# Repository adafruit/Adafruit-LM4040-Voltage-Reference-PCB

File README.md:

## Adafruit LM4040 Voltage Reference PCB
<a href="http://www.adafruit.com/products/2200"><br/>
Click here to purchase one from the Adafruit shop</a>

How good is your multimeter really?  Or maybe your analog converter needs a good reference? Or lets say you want to test your microcontroller's conversion accuracy & precision. If only you had a dependable, high precision, rock-solid voltage reference. Now you know why we made this very cute and useful little breakout board. It has two very high precision shunt-type voltage references with 750 ohm biasing resistors. One is 2.048V (great for 3.3V reference systems) and the other is 4.096 (great for 5V). Both are 0.1% accuracy!

Using is easy, just power with about 5V-12V, or 3V if you want only the 2V reference to work. Then measure the voltage on the output. Note that these are not regulators - you can't power anything off the output. They are for measurements only. For more details, check the LM4040 Datasheet for more information.

PCB files for the Adafruit LM4040 Voltage Reference. The format is EagleCAD schematic and board layout
- https://www.adafruit.com/products/2200

### License

Adafruit invests time and resources providing this open source design, please support Adafruit and open-source hardware by purchasing products from [Adafruit](https://www.adafruit.com)!

All text above must be included in any redistribution

Designed by Limor Fried/Ladyada for Adafruit Industries.
Creative Commons Attribution/Share-Alike, all text above must be included in any redistribution. 
See license.txt for additional information.

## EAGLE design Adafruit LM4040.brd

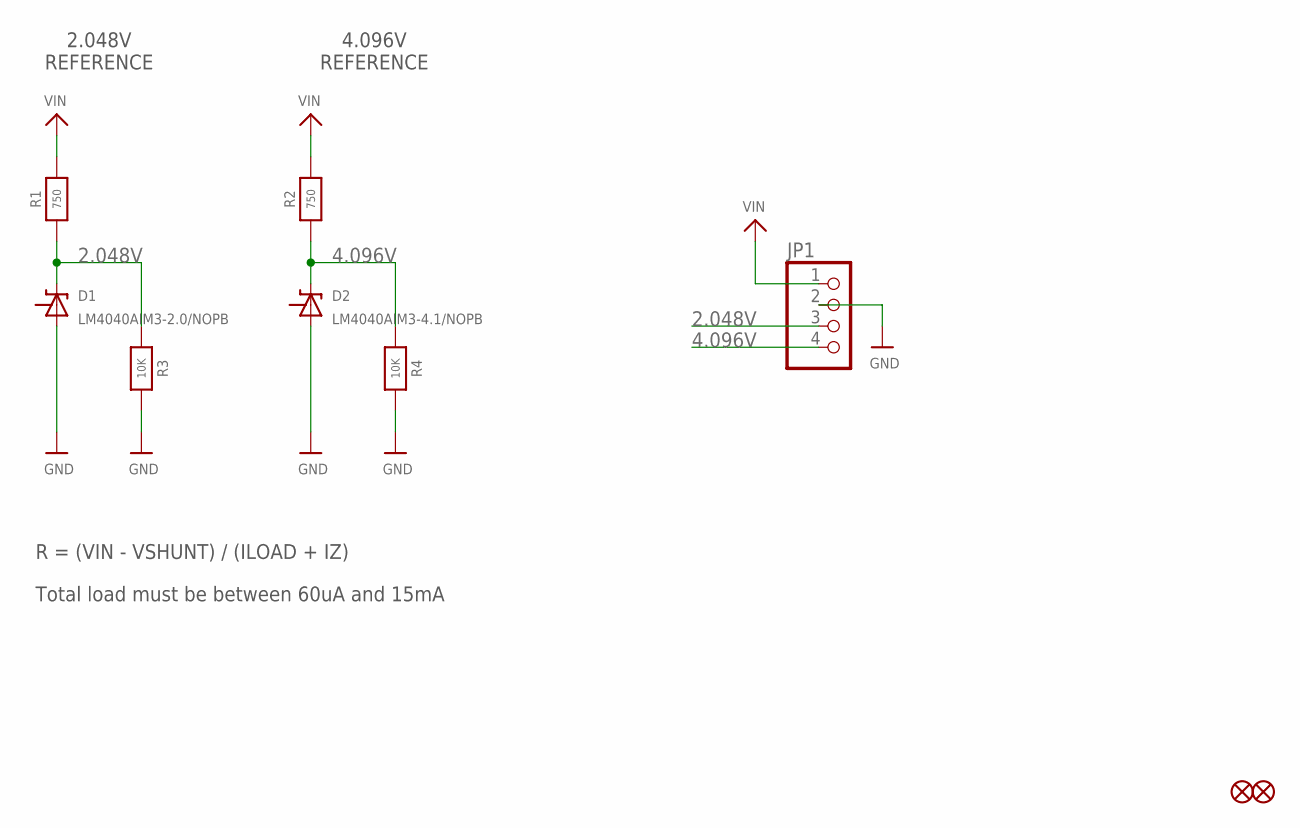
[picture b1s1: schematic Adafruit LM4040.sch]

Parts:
D1: LM4040AIM3-2.0/NOPB; SOT23-R
D2: LM4040AIM3-4.1/NOPB; SOT23-R
FID1, FID2: FIDUCIAL""; FIDUCIAL_1MM
JP1: HEADER-1X4ROUND; 1X04_ROUND
R1, R2: 750; 0805-NO
R3, R4: 10K; 0805-NO

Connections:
2.048V: D1.1 (+), JP1.3, R1.1, R3.1
4.096V: D2.1 (+), JP1.4, R2.1, R4.1
GND: D1.2 (-), D2.2 (-), JP1.2, R3.2, R4.2
VIN: JP1.1, R1.2, R2.2

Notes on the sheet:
2.048V REFERENCE
4.096V REFERENCE
R = (VIN - VSHUNT) / (ILOAD + IZ)
Total load must be between 60uA and 15mA

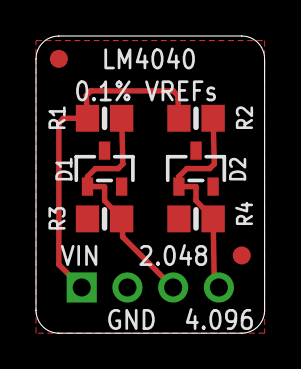
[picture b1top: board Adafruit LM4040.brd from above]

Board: 2 copper layers, 12.7 x 16.5 mm, 10 parts (1 on the bottom side), 4 nets.

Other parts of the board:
U$5: ADAFRUIT_5MM

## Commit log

2016-07-29 init
2026-06-03 update file format to XML

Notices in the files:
parts and their libraries:
microbuilder: This work is placed in the public domain, and may be freely used for commercial and non-commercial work with the following conditions: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
